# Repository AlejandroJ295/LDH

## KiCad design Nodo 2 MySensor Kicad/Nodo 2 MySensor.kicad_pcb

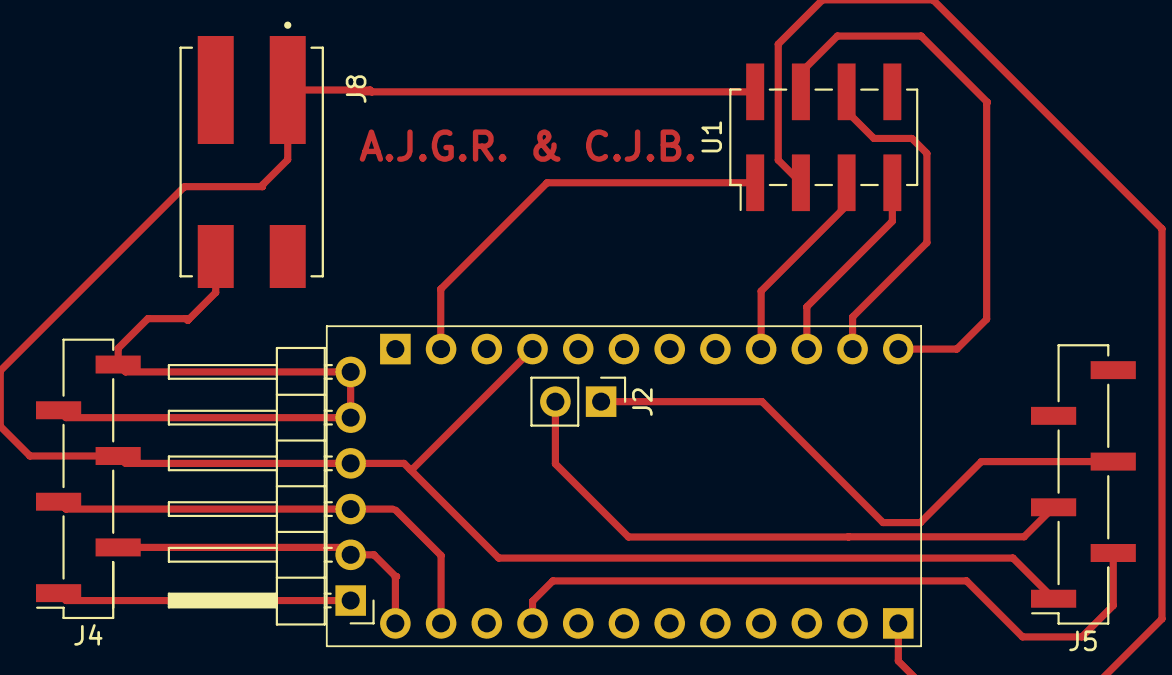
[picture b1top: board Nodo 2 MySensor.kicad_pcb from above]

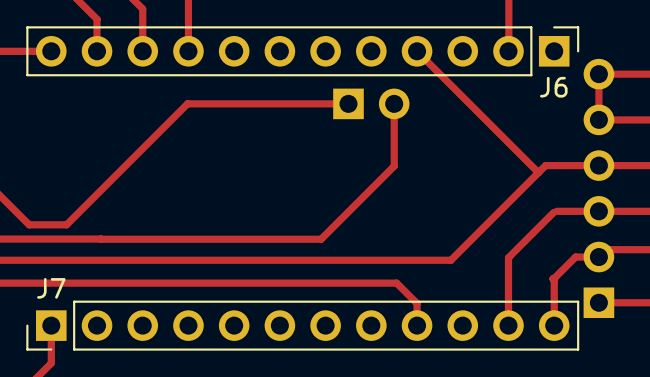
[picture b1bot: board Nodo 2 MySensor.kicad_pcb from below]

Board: 2 copper layers, 8 parts (2 on the bottom side), 13 nets.

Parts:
J1: FTDI; PinHeader_1x06_P2.54mm_Horizontal
J2: I2C; PinHeader_1x02_P2.54mm_Vertical
J4, J5: Conn_01x06_Pin; PinHeader_1x06_P2.54mm_Vertical_SMD_Pin1Right
J6: Analog; PinHeader_1x12_P2.54mm_Vertical
J7: Digital; PinHeader_1x12_P2.54mm_Vertical
J8: 2060-452_998-404; WAGO_2060-452_998-404
U1: NRF24L01_Breakout; PinHeader_2x04_P2.54mm_Vertical_SMD

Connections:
/*D9: J7.1, U1.3 (CE)
/DTR: J1.1, J4.1
/MISO/D12: J6.10, U1.7 (MISO)
/MOSI/*D11: J6.11, U1.6 (MOSI)
/RX: J1.3, J4.3, J7.11
/SCK/D13: J6.9, U1.5 (SCK)
/SCL/A5: J2.2, J5.3
/SDA/A4: J2.1, J5.4
/SS/*D10: J6.12, U1.4 (~CSN)
/TX: J1.2, J4.2, J7.12
/~RESET: J6.3, J7.10
GND: J1.5, J1.6, J4.5, J4.6, J5.2, J6.2, J7.9, J8.2_1 (2), J8.2_2 (2), U1.1 (GND)
VCC: J1.4, J4.4, J5.1, J6.4, J8.1_1 (1), J8.1_2 (1), U1.2 (VCC)

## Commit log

2025-10-07 Primer nodo para el proyecto My Sensor
2025-10-12 Completado el nodo 1, el relay conmuta con los switchs y funciona home assistance
2025-10-14 Nodo 1 completado
2025-10-14 He limpiado el codigo del Nodo 1 y comienzo del Nodo 2
2025-10-21 Bateria
2025-10-22 Battery voltage
2025-10-30 Fin del nodo 2
2025-11-04 Signing añadido
2025-11-06 Completado el proyecto MySensor
2025-11-11 Añadido el proyecto de kicad del nodo 2.
2025-11-13 Diseño del nodo 2 placa
2025-11-19 Nodo 1 esquematico
2025-11-20 Conexion del nodo 1
